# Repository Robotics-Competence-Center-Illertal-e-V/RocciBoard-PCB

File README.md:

# Rocci Board

# Features

* 4x DC Motor outputs a 3 A (motor driver with current limitation)
* 8 separate i2c channels
* low voltage shutdown for battery protection
* i2c fully protected against 12V and reverse polarity
* 3 A switching regulator for 5 V
* 3,3 V with 1 A LDO
* 8 V for Arduino VIN pin
* reverse polarity protection on battery connector
* short circuit protection on all supply pins

# Schematic

[Schematic as pdf](documentation/RocciBoard.pdf)

[Layout as pdf](documentation/RocciBoard__Assembly.pdf)

# Pinout Diagram

## Top

## Bottom

## Hand Assembled Components

male pinheader with femal back:
1* 4
1* 7
2* 8
1* 18x2

male pinheader:
1* 8
1* 10
1* 4
1* 1
9* 4
4* 2

1* XT60 Male

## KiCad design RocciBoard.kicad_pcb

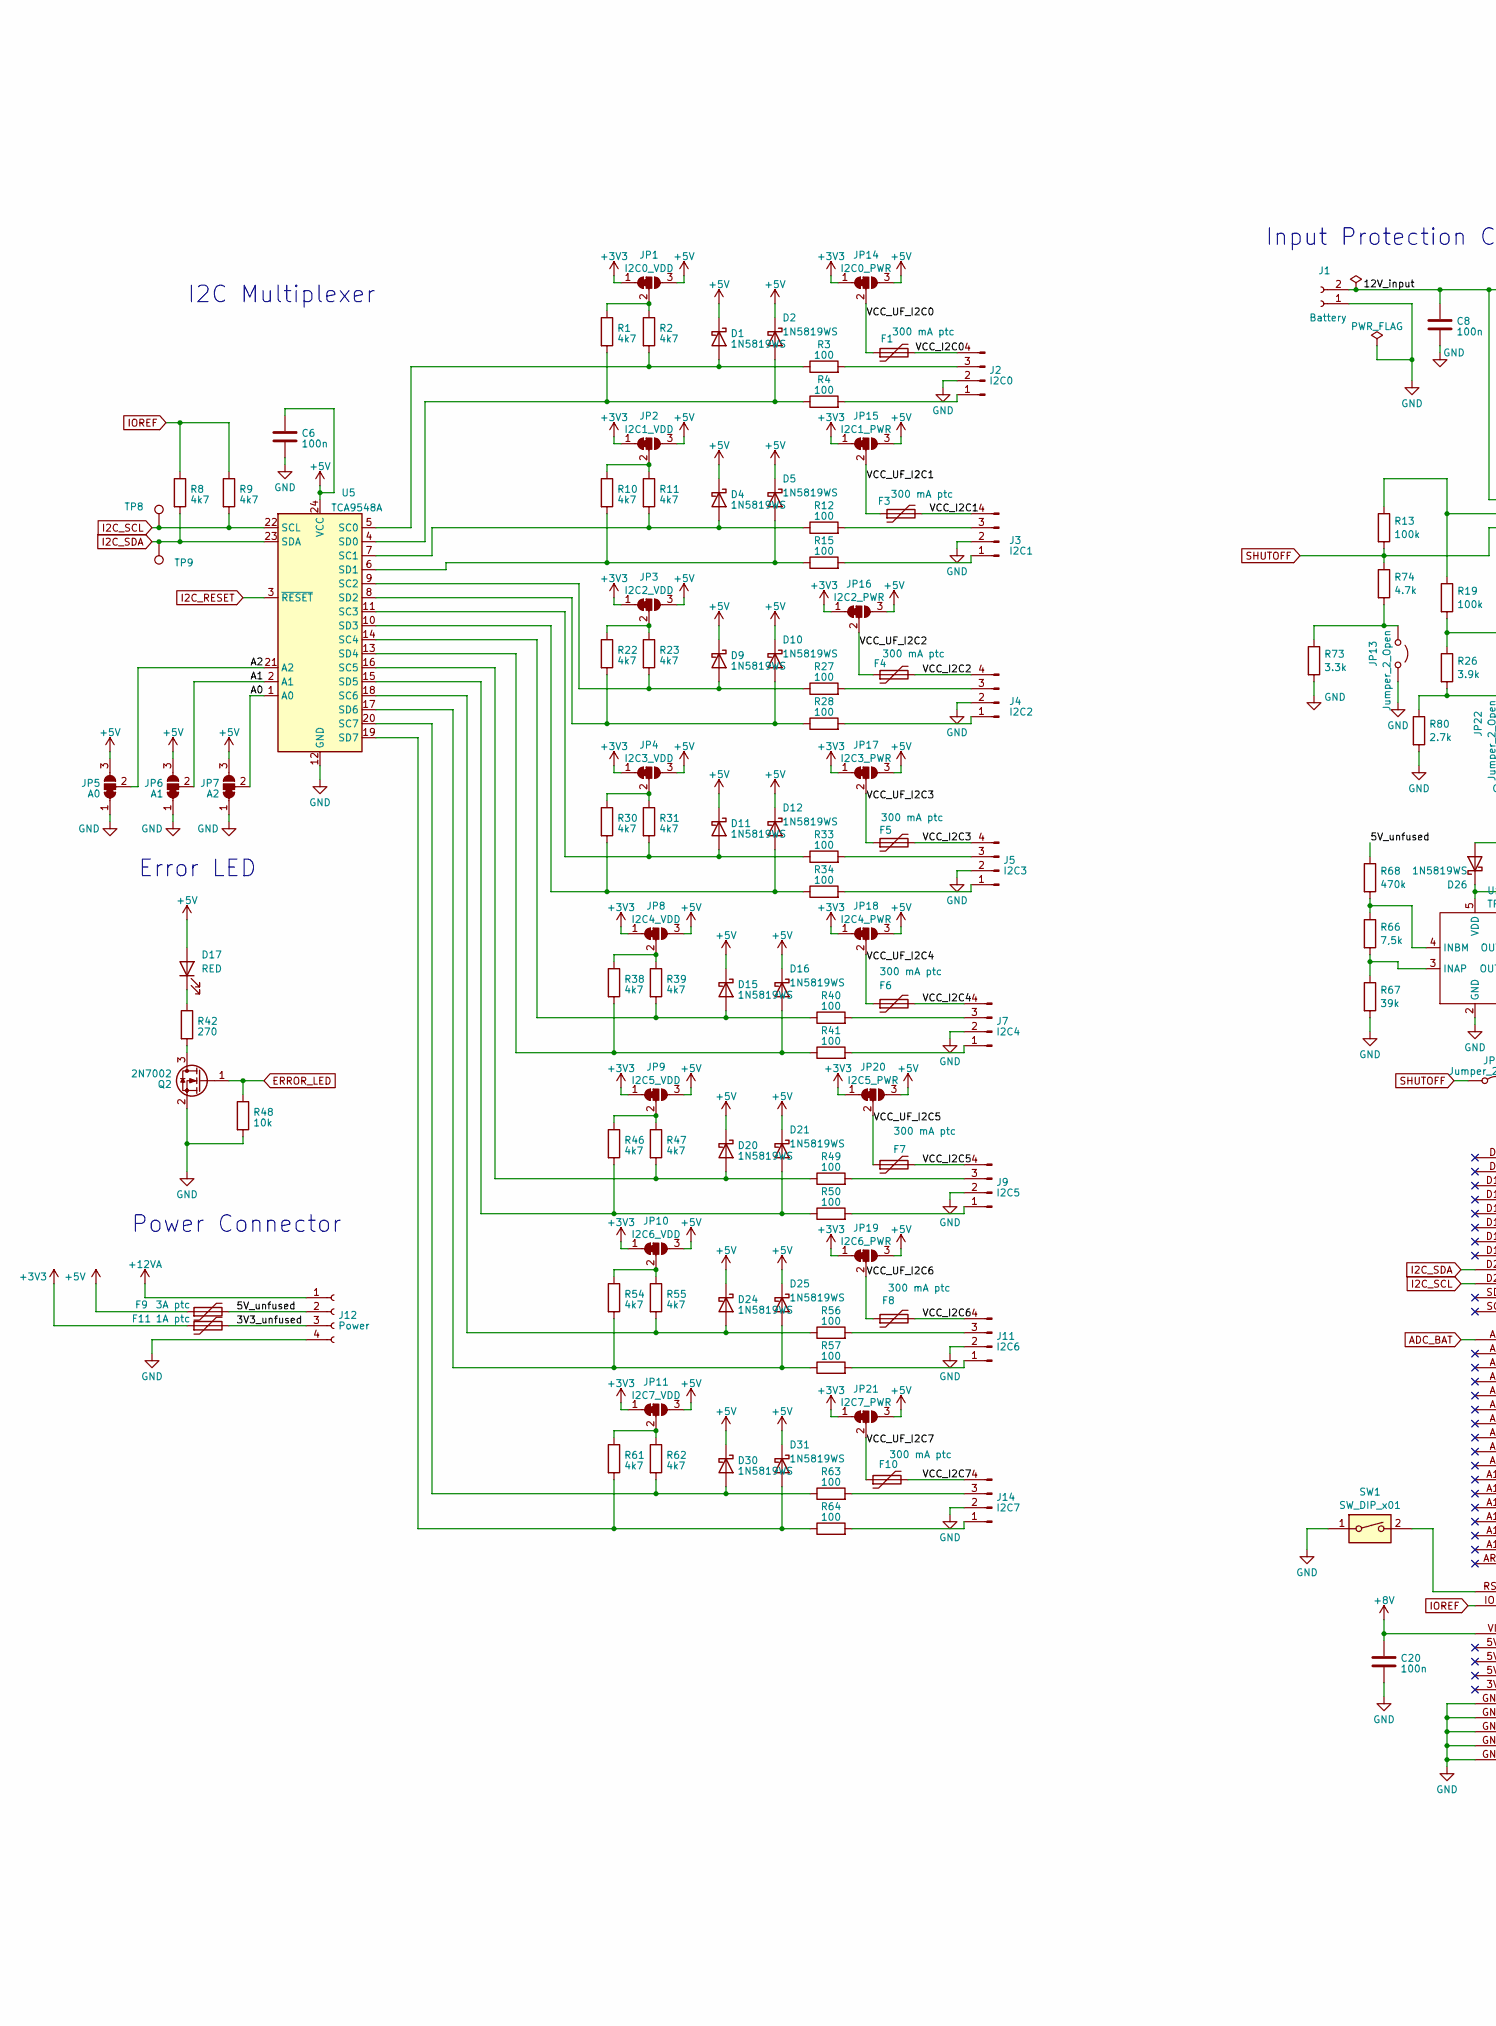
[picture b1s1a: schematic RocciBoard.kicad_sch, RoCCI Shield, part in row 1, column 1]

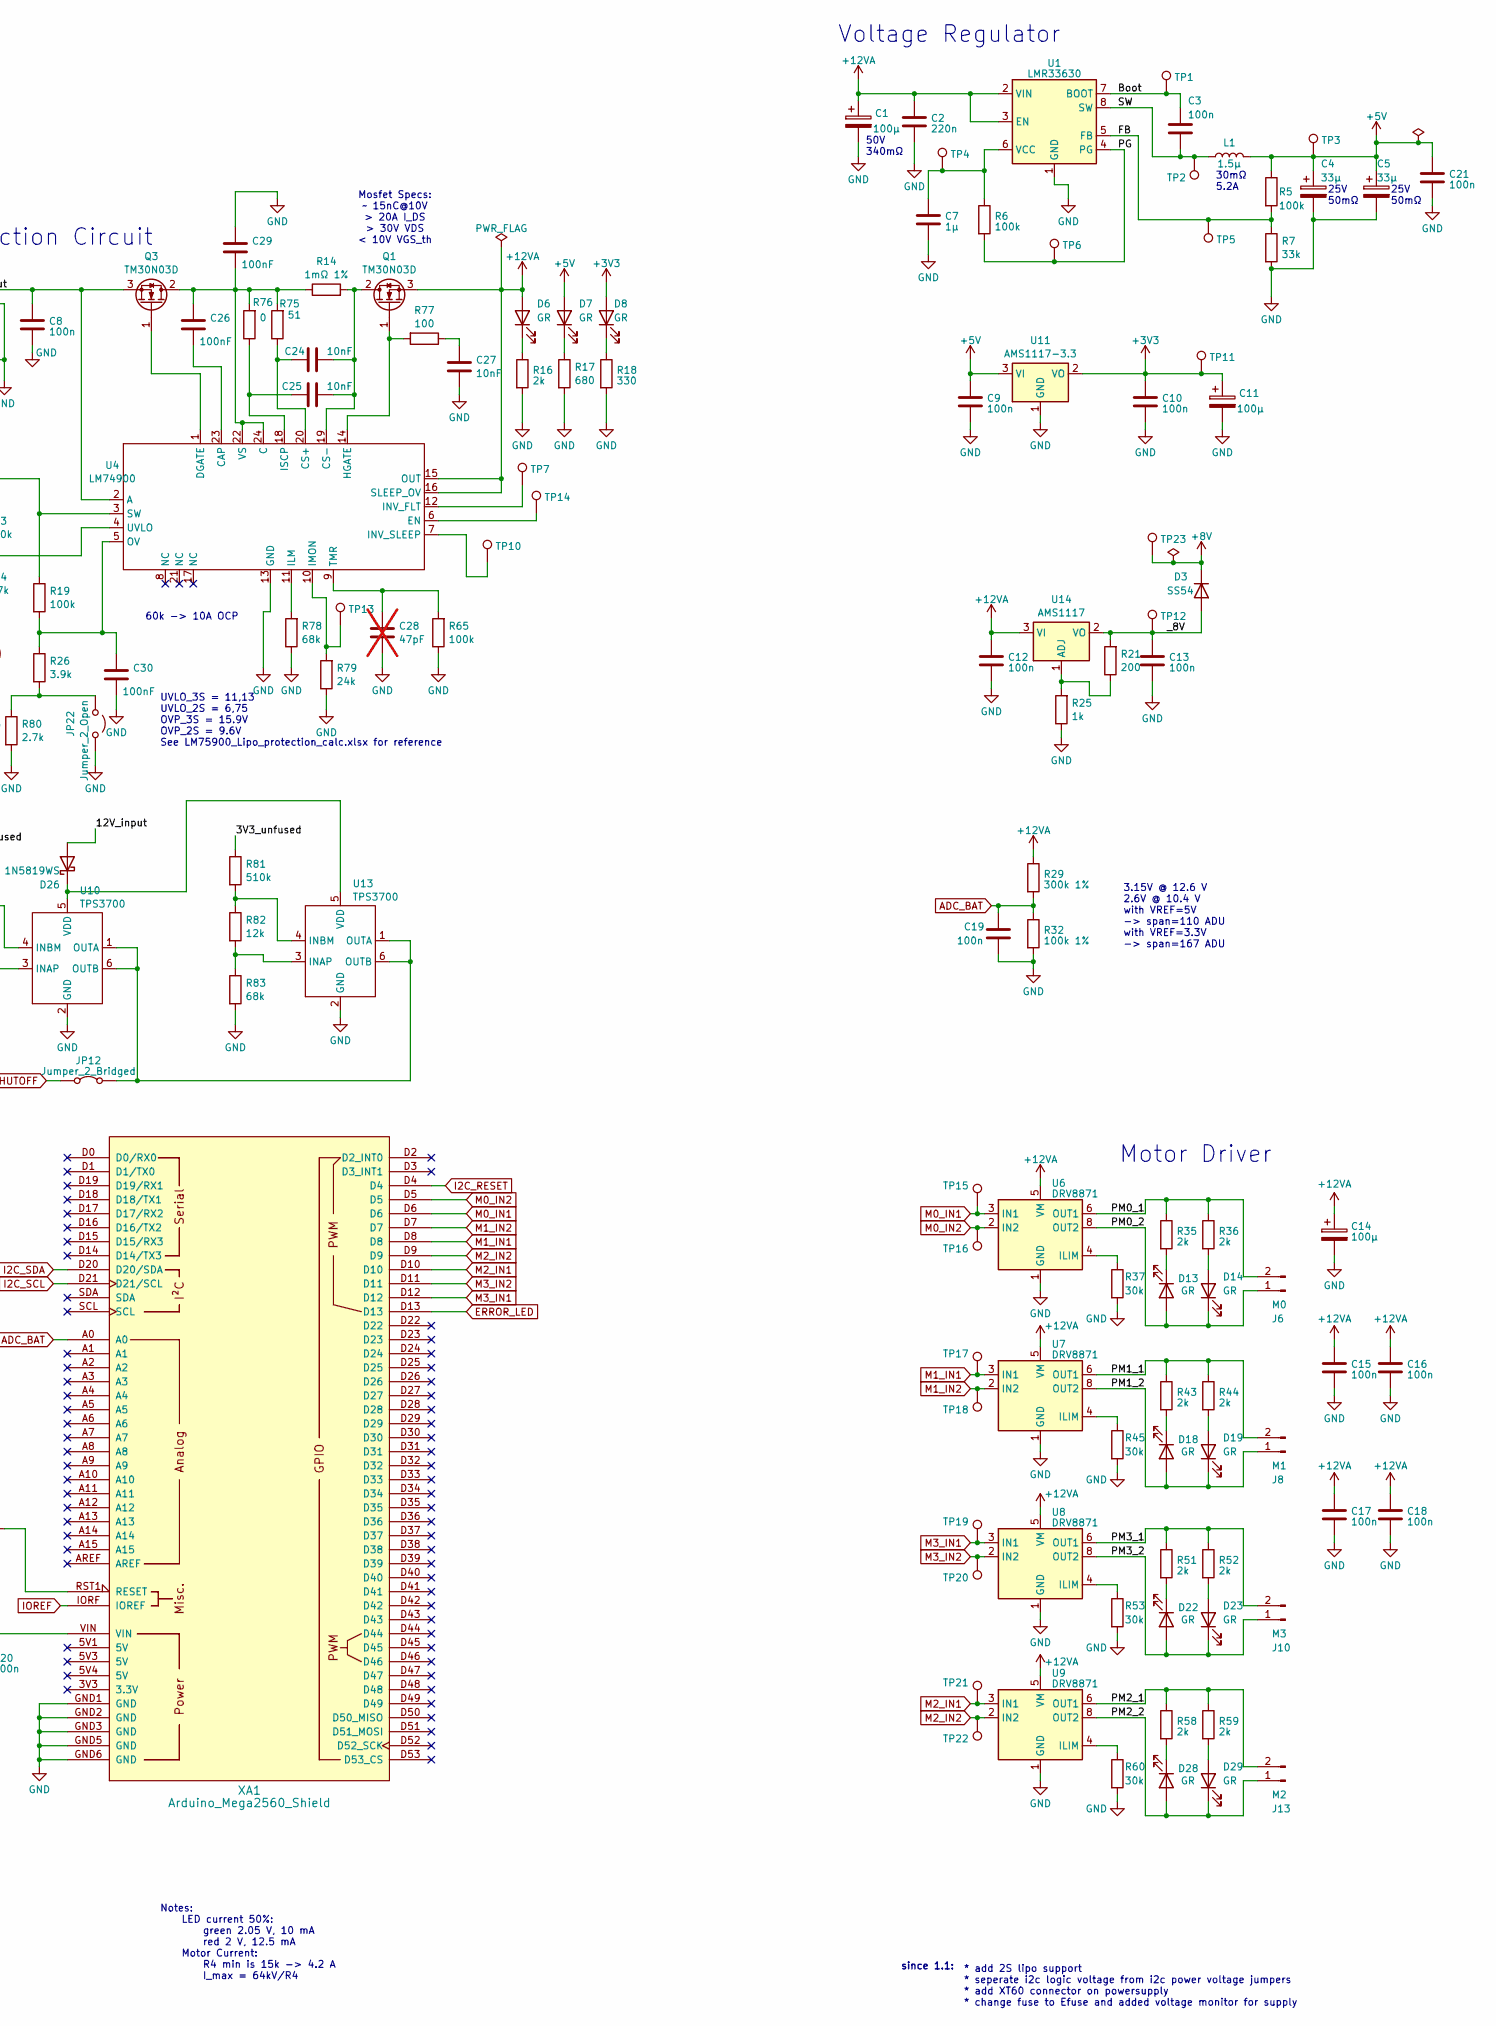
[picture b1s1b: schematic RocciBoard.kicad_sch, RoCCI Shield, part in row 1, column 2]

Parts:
C1, C11, C14: 100µ; CP_Elec_6.3x7.7; LCSC C962164
C2: 220n; C_0603_1608Metric; LCSC C21120
C3, C6, C8, C9, C10, C12, C13, C15, C16, C17, C18, C19, C20, C21: 100n; C_0603_1608Metric; LCSC C14663
C4, C5: 33µ; CP_EIA-7343-43_Kemet-X; LCSC C212716
C7: 1µ; C_0603_1608Metric; LCSC C15849
C24, C25, C27: 10nF; C_0603_1608Metric; LCSC C57112
C26, C29, C30: 100nF; C_0603_1608Metric; LCSC C14663
C28: 47pF; C_0603_1608Metric; LCSC C1671; not fitted
D1, D2, D4, D5, D9, D10, D11, D12, D15, D16, D20, D21, D24, D25, D26, D30, D31: 1N5819WS; D_SOD-323; LCSC C191023
D3: SS54; D_SMA; LCSC C22452
D6, D7, D8, D13, D14, D18, D19, D22, D23, D28, D29: GR; LED_0603_1608Metric; LCSC C965805
D17: RED; LED_0603_1608Metric; LCSC C2286
F1, F3, F4, F5, F6, F7, F8, F10: 300 mA ptc; Fuse_0805_2012Metric; LCSC C261938
F9: 3A ptc; Fuse_2920_7451Metric; LCSC C2977527
F11: 1A ptc; Fuse_1206_3216Metric; LCSC C910830
J1: Battery; AMASS_XT60-M_1x02_P7.20mm_Vertical
J2: I2C0; PinHeader_1x04_P2.54mm_Vertical
J3: I2C1; PinHeader_1x04_P2.54mm_Vertical
J4: I2C2; PinHeader_1x04_P2.54mm_Vertical
J5: I2C3; PinHeader_1x04_P2.54mm_Vertical
J6: M0; PinHeader_1x02_P2.54mm_Vertical
J7: I2C4; PinHeader_1x04_P2.54mm_Vertical
J8: M1; PinHeader_1x02_P2.54mm_Vertical
J9: I2C5; PinHeader_1x04_P2.54mm_Vertical
J10: M3; PinHeader_1x02_P2.54mm_Vertical
J11: I2C6; PinHeader_1x04_P2.54mm_Vertical
J12: Power; PinHeader_1x04_P2.54mm_Vertical
J13: M2; PinHeader_1x02_P2.54mm_Vertical
J14: I2C7; PinHeader_1x04_P2.54mm_Vertical
JP1: I2C0_VDD; SolderJumper-3_P1.3mm_Open_Pad1.0x1.5mm
JP2: I2C1_VDD; SolderJumper-3_P1.3mm_Open_Pad1.0x1.5mm
JP3: I2C2_VDD; SolderJumper-3_P1.3mm_Open_Pad1.0x1.5mm
JP4: I2C3_VDD; SolderJumper-3_P1.3mm_Open_Pad1.0x1.5mm
JP5: A0; SolderJumper-3_P1.3mm_Open_Pad1.0x1.5mm
JP6: A1; SolderJumper-3_P1.3mm_Open_Pad1.0x1.5mm
JP7: A2; SolderJumper-3_P1.3mm_Open_Pad1.0x1.5mm
JP8: I2C4_VDD; SolderJumper-3_P1.3mm_Open_Pad1.0x1.5mm
JP9: I2C5_VDD; SolderJumper-3_P1.3mm_Open_Pad1.0x1.5mm
JP10: I2C6_VDD; SolderJumper-3_P1.3mm_Open_Pad1.0x1.5mm
JP11: I2C7_VDD; SolderJumper-3_P1.3mm_Open_Pad1.0x1.5mm
JP12: Jumper_2_Bridged; SolderJumper-2_P1.3mm_Open_Pad1.0x1.5mm
JP13, JP22: Jumper_2_Open; SolderJumper-2_P1.3mm_Open_Pad1.0x1.5mm
JP14: I2C0_PWR; SolderJumper-3_P1.3mm_Open_Pad1.0x1.5mm
JP15: I2C1_PWR; SolderJumper-3_P1.3mm_Open_Pad1.0x1.5mm
JP16: I2C2_PWR; SolderJumper-3_P1.3mm_Open_Pad1.0x1.5mm
JP17: I2C3_PWR; SolderJumper-3_P1.3mm_Open_Pad1.0x1.5mm
JP18: I2C4_PWR; SolderJumper-3_P1.3mm_Open_Pad1.0x1.5mm
JP19: I2C6_PWR; SolderJumper-3_P1.3mm_Open_Pad1.0x1.5mm
JP20: I2C5_PWR; SolderJumper-3_P1.3mm_Open_Pad1.0x1.5mm
JP21: I2C7_PWR; SolderJumper-3_P1.3mm_Open_Pad1.0x1.5mm
L1: 1.5µ; L_Sunlord_SWPA4020S; LCSC C98360
Q1, Q3: TM30N03D; TO-252-2; LCSC C18186756
Q2: 2N7002; SOT-23; LCSC C8545
R1, R2, R8, R9, R10, R11, R22, R23, R30, R31, R38, R39, R46, R47, R54, R55, R61, R62: 4k7; R_0603_1608Metric; LCSC C23162
R3, R4, R12, R15, R27, R28, R33, R34, R40, R41, R49, R50, R56, R57, R63, R64, R77: 100; R_0603_1608Metric; LCSC C22775
R5, R6, R13, R19, R65: 100k; R_0603_1608Metric; LCSC C25803
R7: 33k; R_0603_1608Metric; LCSC C4216
R14: 1mΩ 1%; R_1206_3216Metric; LCSC C7467246
R16, R35, R36, R43, R44, R51, R52, R58, R59: 2k; R_0603_1608Metric; LCSC C22975
R17: 680; R_0603_1608Metric; LCSC C23228
R18: 330; R_0603_1608Metric; LCSC C23138
R21: 200; R_0603_1608Metric; LCSC C8218
R25: 1k; R_0603_1608Metric; LCSC C21190
R26: 3.9k; R_0603_1608Metric; LCSC C23018
R29: 300k 1%; R_0603_1608Metric; LCSC C23024
R32: 100k 1%; R_0603_1608Metric; LCSC C25803
R37, R45, R53, R60: 30k; R_0805_2012Metric; LCSC C22984
R42: 270; R_0603_1608Metric; LCSC C22966
R48: 10k; R_0603_1608Metric; LCSC C25804
R66: 7,5k; R_0603_1608Metric; LCSC C23234
R67: 39k; R_0603_1608Metric; LCSC C23153
R68: 470k; R_0603_1608Metric; LCSC C23178
R73: 3.3k; R_0603_1608Metric; LCSC C22978
R74: 4.7k; R_0603_1608Metric; LCSC C23162
R75: 51; R_0603_1608Metric; LCSC C23197
R76: 0; R_0603_1608Metric; LCSC C21189
R78, R83: 68k; R_0603_1608Metric; LCSC C23231
R79: 24k; R_0603_1608Metric; LCSC C23352
R80: 2.7k; R_0603_1608Metric; LCSC C13167
R81: 510k; R_0603_1608Metric; LCSC C23192
R82: 12k; R_0603_1608Metric; LCSC C22790
SW1: SW_DIP_x01; SW_Push_1P1T_XKB_TS-1187A; LCSC C318884
TP1, TP2, TP3, TP4, TP5, TP6, TP7, TP8, TP9, TP10, TP11, TP12, TP13, TP14, TP15, TP16, TP17, TP18, TP19, TP20, TP21, TP22, TP23: TestPoint_Pad_D1.0mm
U1: LMR33630; Texas_HSOP-8-1EP_3.9x4.9mm_P1.27mm_ThermalVias; LCSC C841384
U4: LM74900; VQFN-24-1EP_4x4mm_P0.5mm_EP2.5x2.5mm_ThermalVias; LCSC C20345498
U5: TCA9548A; TSSOP-24_4.4x7.8mm_P0.65mm; LCSC C130026
U6, U7, U8, U9: DRV8871; Texas_HTSOP-8-1EP_3.9x4.9mm_P1.27mm_EP2.95x4.9mm_Mask2.4x3.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; LCSC C75864
U10, U13: TPS3700; SOT-23-6; LCSC C33002
U11: AMS1117-3.3; SOT-223-3_TabPin2; LCSC C6186
U14: AMS1117; SOT-223-3_TabPin2; LCSC C347224
XA1: Arduino_Mega2560_Shield; Arduino_Mega2560_custom_Shield

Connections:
+3V3: C10.1, C11.1, D8.2 (A), F11.1, JP1.1 (A), JP2.1 (A), JP3.1 (A), JP4.1 (A), JP8.1 (A), JP9.1 (A), JP10.1 (A), JP11.1 (A), JP14.1 (A), JP15.1 (A), JP16.1 (A), JP17.1 (A), JP18.1 (A), JP19.1 (A), JP20.1 (A), JP21.1 (A), TP11.1, U11.2 (VO)
+5V: C4.1, C5.1, C6.1, C9.1, C21.1, D1.1 (K), D2.1 (K), D4.1 (K), D5.1 (K), D7.2 (A), D9.1 (K), D10.1 (K), D11.1 (K), D12.1 (K), D15.1 (K), D16.1 (K), D17.2 (A), D20.1 (K), D21.1 (K), D24.1 (K), D25.1 (K), D30.1 (K), D31.1 (K), F9.1, JP1.3 (B), JP2.3 (B), JP3.3 (B), JP4.3 (B), JP5.3 (B), JP6.3 (B), JP7.3 (B), JP8.3 (B), JP9.3 (B), JP10.3 (B), JP11.3 (B), JP14.3 (B), JP15.3 (B), JP16.3 (B), JP17.3 (B), JP18.3 (B), JP19.3 (B), JP20.3 (B), JP21.3 (B), L1.2, R5.1, TP3.1, U5.24 (VCC), U11.3 (VI)
+8V: C20.1, D3.1 (K), TP23.1, XA1.VIN
+12VA: C1.1, C2.1, C12.1, C14.1, C15.1, C16.1, C17.1, C18.1, D6.2 (A), J12.1, Q1.3 (S), R29.1, U1.2 (VIN), U1.3 (EN), U4.15 (OUT), U4.16 (SLEEP_OV), U6.5 (VM), U7.5 (VM), U8.5 (VM), U9.5 (VM), U14.3 (VI)
/3V3_unfused: F11.2, J12.3, R81.1
/5V_unfused: F9.2, J12.2, R68.1
/12V_input: C8.1, D26.2 (A), J1.2, Q3.3 (S), U4.2 (A)
/A0: JP7.2 (C), U5.1 (A0)
/A1: JP6.2 (C), U5.2 (A1)
/A2: JP5.2 (C), U5.21 (A2)
/Boot: C3.1, TP1.1, U1.7 (BOOT)
/FB: R5.2, R7.1, TP5.1, U1.5 (FB)
/PG: R6.2, TP6.1, U1.4 (PG)
/PM0_1: J6.2, R35.1, R36.1, U6.6 (OUT1)
/PM0_2: D13.2 (A), D14.1 (K), J6.1, U6.8 (OUT2)
/PM1_1: J8.2, R43.1, R44.1, U7.6 (OUT1)
/PM1_2: D18.2 (A), D19.1 (K), J8.1, U7.8 (OUT2)
/PM2_1: J13.2, R58.1, R59.1, U9.6 (OUT1)
/PM2_2: D28.2 (A), D29.1 (K), J13.1, U9.8 (OUT2)
/PM3_1: J10.2, R51.1, R52.1, U8.6 (OUT1)
/PM3_2: D22.2 (A), D23.1 (K), J10.1, U8.8 (OUT2)
/SW: C3.2, L1.1, TP2.1, U1.8 (SW)
/VCC_I2C0: F1.2, J2.4
/VCC_I2C1: F3.2, J3.4
/VCC_I2C2: F4.2, J4.4
/VCC_I2C3: F5.2, J5.4
/VCC_I2C4: F6.2, J7.4
/VCC_I2C5: F7.2, J9.4
/VCC_I2C6: F8.2, J11.4
/VCC_I2C7: F10.2, J14.4
/VCC_UF_I2C0: F1.1, JP14.2 (C)
/VCC_UF_I2C1: F3.1, JP15.2 (C)
/VCC_UF_I2C2: F4.1, JP16.2 (C)
/VCC_UF_I2C3: F5.1, JP17.2 (C)
/VCC_UF_I2C4: F6.1, JP18.2 (C)
/VCC_UF_I2C5: F7.1, JP20.2 (C)
/VCC_UF_I2C6: F8.1, JP19.2 (C)
/VCC_UF_I2C7: F10.1, JP21.2 (C)
/_8V: C13.1, D3.2 (A), R21.2, TP12.1, U14.2 (VO)
ADC_BAT: C19.2, R29.2, R32.1, XA1.A0
ERROR_LED: Q2.1 (G), R48.1, XA1.D13
GND: C1.2, C2.2, C4.2, C5.2, C6.2, C7.2, C8.2, C9.2, C10.2, C11.2, C12.2, C13.2, C14.2, C15.2, C16.2, C17.2, C18.2, C19.1, C20.2, C21.2, C27.2, C28.2, C29.1, C30.2, J1.1, J2.2, J3.2, J4.2, J5.2, J7.2, J9.2, J11.2, J12.4, J14.2, JP5.1 (A), JP6.1 (A), JP7.1 (A), JP13.2 (B), JP22.2 (B), Q2.2 (S), R7.2, R16.2, R17.2, R18.2, R25.1, R32.2, R37.2, R45.2, R48.2, R53.2, R60.2, R65.1, R67.2, R73.2, R78.1, R79.1, R80.2, R83.2, SW1.1, U1.1 (GND), U1.9 (GND), U4.13 (GND), U5.12 (GND), U6.1 (GND), U6.7 (GND), U6.9 (GND), U7.1 (GND), U7.7 (GND), U7.9 (GND), U8.1 (GND), U8.7 (GND), U8.9 (GND), U9.1 (GND), U9.7 (GND), U9.9 (GND), U10.2 (GND), U11.1 (GND), U13.2 (GND), XA1.GND1 (GND), XA1.GND2 (GND), XA1.GND3 (GND), XA1.GND5 (GND), XA1.GND6 (GND)
I2C_RESET: U5.3 (~RESET), XA1.D4
I2C_SCL: R9.2, TP8.1, U5.22 (SCL), XA1.D21 (D21/SCL)
I2C_SDA: R8.2, TP9.1, U5.23 (SDA), XA1.D20 (D20/SDA)
IOREF: R8.1, R9.1, XA1.IORF (IOREF)
M0_IN1: TP15.1, U6.3 (IN1), XA1.D6
M0_IN2: TP16.1, U6.2 (IN2), XA1.D5
M1_IN1: TP17.1, U7.3 (IN1), XA1.D8
M1_IN2: TP18.1, U7.2 (IN2), XA1.D7
M2_IN1: TP21.1, U9.3 (IN1), XA1.D10
M2_IN2: TP22.1, U9.2 (IN2), XA1.D9
M3_IN1: TP19.1, U8.3 (IN1), XA1.D12
M3_IN2: TP20.1, U8.2 (IN2), XA1.D11
unnamed: C27.1, R77.1
unnamed: D1.2 (A), R2.2, R3.1, U5.5 (SC0)
unnamed: D2.2 (A), R1.2, R4.1, U5.4 (SD0)
unnamed: D4.2 (A), R11.2, R12.1, U5.7 (SC1)
unnamed: D5.2 (A), R10.2, R15.1, U5.6 (SD1)
unnamed: D6.1 (K), R16.1
unnamed: D7.1 (K), R17.1
unnamed: D8.1 (K), R18.1
unnamed: D9.2 (A), R23.2, R27.1, U5.9 (SC2)
unnamed: D10.2 (A), R22.2, R28.1, U5.8 (SD2)
unnamed: D11.2 (A), R31.2, R33.1, U5.11 (SC3)
unnamed: D12.2 (A), R30.2, R34.1, U5.10 (SD3)
unnamed: D13.1 (K), R35.2
unnamed: D14.2 (A), R36.2
unnamed: D15.2 (A), R39.2, R40.1, U5.14 (SC4)
unnamed: D16.2 (A), R38.2, R41.1, U5.13 (SD4)
unnamed: D17.1 (K), R42.1
unnamed: D18.1 (K), R43.2
unnamed: D19.2 (A), R44.2
unnamed: D20.2 (A), R47.2, R49.1, U5.16 (SC5)
unnamed: D21.2 (A), R46.2, R50.1, U5.15 (SD5)
unnamed: D22.1 (K), R51.2
unnamed: D23.2 (A), R52.2
unnamed: D24.2 (A), R55.2, R56.1, U5.18 (SC6)
unnamed: D25.2 (A), R54.2, R57.1, U5.17 (SD6)
unnamed: D26.1 (K), U10.5 (VDD), U13.5 (VDD)
unnamed: D28.1 (K), R58.2
unnamed: D29.2 (A), R59.2
unnamed: D30.2 (A), R62.2, R63.1, U5.20 (SC7)
unnamed: D31.2 (A), R61.2, R64.1, U5.19 (SD7)
unnamed: J2.1, R4.2
unnamed: J2.3, R3.2
unnamed: J3.1, R15.2
unnamed: J3.3, R12.2
unnamed: J4.1, R28.2
unnamed: J4.3, R27.2
unnamed: J5.1, R34.2
unnamed: J5.3, R33.2
unnamed: J7.1, R41.2
unnamed: J7.3, R40.2
unnamed: J9.1, R50.2
unnamed: J9.3, R49.2
unnamed: J11.1, R57.2
unnamed: J11.3, R56.2
unnamed: J14.1, R64.2
unnamed: J14.3, R63.2
unnamed: JP1.2 (C), R1.1, R2.1
unnamed: JP2.2 (C), R10.1, R11.1
unnamed: JP3.2 (C), R22.1, R23.1
unnamed: JP4.2 (C), R30.1, R31.1
unnamed: JP8.2 (C), R38.1, R39.1
unnamed: JP9.2 (C), R46.1, R47.1
unnamed: JP10.2 (C), R54.1, R55.1
unnamed: JP11.2 (C), R61.1, R62.1
unnamed: JP12.2 (B), U10.1 (OUTA), U10.6 (OUTB), U13.1 (OUTA), U13.6 (OUTB)
unnamed: JP13.1 (A), R73.1, R74.2
unnamed: JP22.1 (A), R26.2, R80.1
unnamed: C24.2, C25.2, Q1.2 (D), R14.2, U4.19 (CS-)
unnamed: Q1.1 (G), R77.2, U4.14 (HGATE)
unnamed: Q2.3 (D), R42.2
unnamed: C26.1, C29.2, Q3.2 (D), R14.1, R75.2, R76.2, U4.22 (VS), U4.24 (C)
unnamed: Q3.1 (G), U4.1 (DGATE)
unnamed: C7.1, R6.1, TP4.1, U1.6 (VCC)
unnamed: C26.2, U4.23 (CAP)
unnamed: C24.1, R75.1, U4.20 (CS+)
unnamed: TP14.1, U4.6 (EN)
unnamed: R78.2, U4.11 (ILM)
unnamed: R79.2, TP13.1, U4.10 (IMON)
unnamed: TP7.1, U4.12 (INV_FLT)
unnamed: TP10.1, U4.7 (INV_SLEEP)
unnamed: C25.1, R76.1, U4.18 (ISCP)
unnamed: C30.1, R19.2, R26.1, U4.5 (OV)
unnamed: R13.1, R19.1, U4.3 (SW)
unnamed: C28.1, R65.2, U4.9 (TMR)
unnamed: R37.1, U6.4 (ILIM)
unnamed: R45.1, U7.4 (ILIM)
unnamed: R53.1, U8.4 (ILIM)
unnamed: R60.1, U9.4 (ILIM)
unnamed: R66.2, R67.1, U10.3 (INAP)
unnamed: R66.1, R68.2, U10.4 (INBM)
unnamed: R82.2, R83.1, U13.3 (INAP)
unnamed: R81.2, R82.1, U13.4 (INBM)
unnamed: R21.1, R25.2, U14.1 (ADJ)
unnamed: SW1.2, XA1.RST1 (RESET)
SHUTOFF: JP12.1 (A), R13.2, R74.1, U4.4 (UVLO)

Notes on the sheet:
Notes: LED current 50%: green 2.05 V, 10 mA red 2 V, 12.5 mA Motor Current: R4 min is 15k -> 4.2 A I_max = 64kV/R4
Error LED
30mΩ 5.2A
Mosfet Specs: ~ 15nC@10V > 20A I_DS > 30V VDS < 10V VGS_th
3.15V @ 12.6 V 2.6V @ 10.4 V with VREF=5V -> span=110 ADU with VREF=3.3V -> span=167 ADU
Motor Driver
since 1.1:
50V 340mΩ
60k -> 10A OCP
UVLO_3S = 11,13 UVLO_2S = 6,75 OVP_3S = 15.9V OVP_2S = 9.6V See LM75900_Lipo_protection_calc.xlsx for reference
Input Protection Circuit
25V 50mΩ
I2C Multiplexer
Power Connector
* add 2S lipo support * seperate i2c logic voltage from i2c power voltage jumpers * add XT60 connector on powersupply * change fuse to Efuse and added voltage monitor for supply
Voltage Regulator

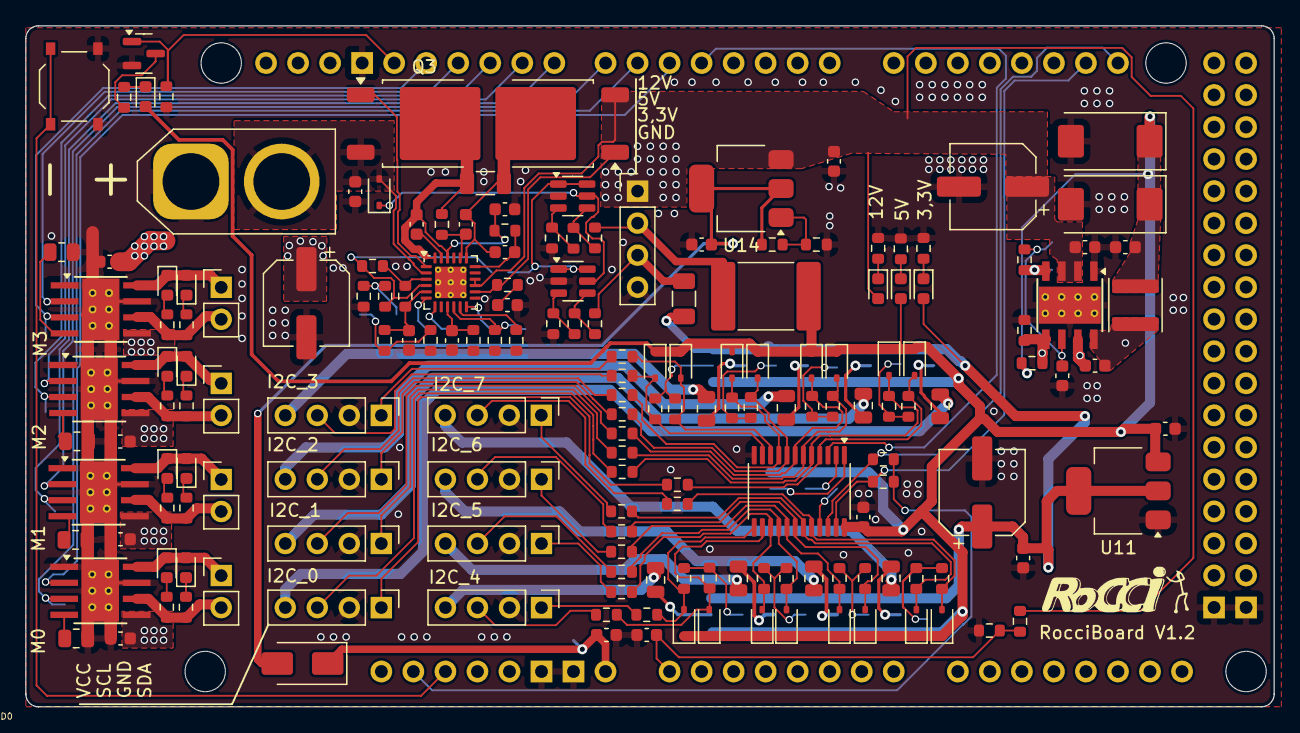
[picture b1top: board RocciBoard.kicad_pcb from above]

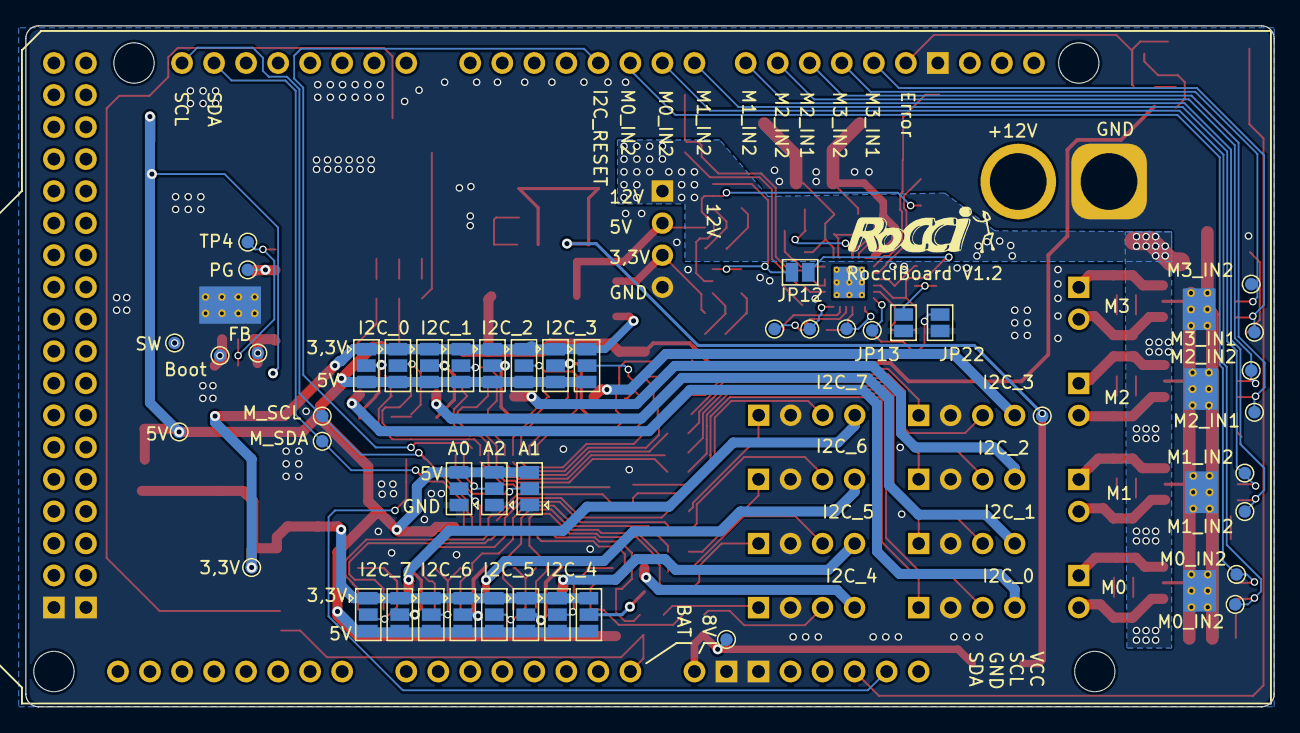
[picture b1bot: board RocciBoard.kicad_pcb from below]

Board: 2 copper layers, 99.0 x 54.0 mm, 221 parts (45 on the bottom side), 139 nets.

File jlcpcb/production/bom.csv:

Designator,Footprint,Quantity,Value,LCSC Part #
"C1, C11, C14",CP_Elec_6.3x7.7,3,100µ,C962164
"C10, C12, C13, C15, C16, C17, C18, C19, C20, C21, C3, C6, C8, C9",0603,14,100n,C14663
C2,0603,1,220n,C21120
"C4, C5",CP_EIA-7343-43_Kemet-X,2,33µ,C212716
C7,0603,1,1µ,C15849
"D1, D10, D11, D12, D15, D16, D2, D20, D21, D24, D25, D30, D31, D4, D5, D9",D_SOD-323,16,1N5819WS,C191023
"D13, D14, D18, D19, D22, D23, D28, D29, D6, D7, D8",0603,11,GR,C72043
D17,0603,1,RED,C2286
D3,D_SMA,1,SS54,C22452
D32,TO-277A,1,SB10100L,C113946
"F1, F10, F3, F4, F5, F6, F7, F8",0805,8,300 mA ptc,C261938
F11,1206,1,1A ptc,C910830
F2,Fuseholder_Cylinder-5x20mm_Wuerth_696103101002-SMD_Horizontal_Open,1,10A,C122783
F9,2920,1,3A ptc,C2977527
J1,"PhoenixContact_MSTBVA_2,5_2-G_1x02_P5.00mm_Vertical",1,Battery,
J10,PinHeader_1x02_P2.54mm_Vertical,1,M3,
J11,PinHeader_1x04_P2.54mm_Vertical,1,I2C6,
J12,PinHeader_1x04_P2.54mm_Vertical,1,Power,
J13,PinHeader_1x02_P2.54mm_Vertical,1,M2,
J14,PinHeader_1x04_P2.54mm_Vertical,1,I2C7,
J2,PinHeader_1x04_P2.54mm_Vertical,1,I2C0,
J3,PinHeader_1x04_P2.54mm_Vertical,1,I2C1,
J4,PinHeader_1x04_P2.54mm_Vertical,1,I2C2,
J5,PinHeader_1x04_P2.54mm_Vertical,1,I2C3,
J6,PinHeader_1x02_P2.54mm_Vertical,1,M0,
J7,PinHeader_1x04_P2.54mm_Vertical,1,I2C4,
J8,PinHeader_1x02_P2.54mm_Vertical,1,M1,
J9,PinHeader_1x04_P2.54mm_Vertical,1,I2C5,
JP1,SolderJumper-3_P1.3mm_Open_Pad1.0x1.5mm,1,I2C0_VCC,
JP10,SolderJumper-3_P1.3mm_Open_Pad1.0x1.5mm,1,I2C6_VCC,
JP11,SolderJumper-3_P1.3mm_Open_Pad1.0x1.5mm,1,I2C7_VCC,
JP12,SolderJumper-2_P1.3mm_Open_Pad1.0x1.5mm,1,Jumper_2_Bridged,
JP2,SolderJumper-3_P1.3mm_Open_Pad1.0x1.5mm,1,I2C1_VCC,
JP3,SolderJumper-3_P1.3mm_Open_Pad1.0x1.5mm,1,I2C2_VCC,
JP4,SolderJumper-3_P1.3mm_Open_Pad1.0x1.5mm,1,I2C3_VCC,
JP5,SolderJumper-3_P1.3mm_Open_Pad1.0x1.5mm,1,A0,
JP6,SolderJumper-3_P1.3mm_Open_Pad1.0x1.5mm,1,A1,
JP7,SolderJumper-3_P1.3mm_Open_Pad1.0x1.5mm,1,A2,
JP8,SolderJumper-3_P1.3mm_Open_Pad1.0x1.5mm,1,I2C4_VCC,
JP9,SolderJumper-3_P1.3mm_Open_Pad1.0x1.5mm,1,I2C5_VCC,
L1,L_Sunlord_SWPA4020S,1,1.5µ,C98360
Q1,SOIC-8_3.9x4.9mm_P1.27mm,1,IRF 7424,C148149
Q2,SOT-23,1,2N7002,C8545
"R1, R10, R11, R2, R22, R23, R30, R31, R38, R39, R46, R47, R54, R55, R61, R62, R8, R9",0603,18,4k7,C23162
"R12, R15, R27, R28, R3, R33, R34, R4, R40, R41, R49, R50, R56, R57, R63, R64",0603,16,100,C22775
R13,0603,1,4700k 1%,C23163
"R14, R48",0603,2,10k,C25804
"R16, R35, R36, R43, R44, R51, R52, R58, R59, R72",0603,10,2k,C22975
R17,0603,1,620,C23228
R18,0603,1,330,C23138
R19,0603,1,10k 1%,C25804
"R20, R21",0603,2,240,C23350
R24,0603,1,390,C23151
"R25, R70",0603,2,1k3,C22767
R26,0603,1,180k 1%,C22827
R29,0603,1,300k 1%,C23024
R32,0603,1,100k 1%,C25803
"R37, R45, R53, R60",0805,4,30k,C22984
R42,0603,1,270,C22966
"R5, R6",0603,2,100k,C25803
"R65, R71",0603,2,1k,C21190
R69,0603,1,1k5,C22843
R7,0603,1,24.9k,C25962
RESET,SW_Push_1P1T_XKB_TS-1187A,1,SW_DIP_x01,C318884
"TP1, TP10, TP11, TP12, TP13, TP14, TP15, TP16, TP17, TP18, TP19, TP2, TP20, TP21, TP22, TP23, TP3, TP4, TP5, TP6, TP7, TP8, TP9",TestPoint_Pad_D1.0mm,23,~,
U1,Texas_HSOP-8-1EP_3.9x4.9mm_P1.27mm_ThermalVias,1,LMR33630,C841384
"U11, U12",SOT-23,2,CJ431,C3113
"U2, U3",TO-252-2,2,LM317_TO-252,C75510
U4,SOT-23-6,1,TPS3700,C3658987
U5,TSSOP-24_4.4x7.8mm_P0.65mm,1,TCA9548A,C130026
"U6, U7, U8, U9",Texas_HTSOP-8-1EP_3.9x4.9mm_P1.27mm_EP2.95x4.9mm_Mask2.4x3.1mm_ThermalVias,4,DRV8871,C75864
XA1,Arduino_Mega2560_custom_Shield,1,Arduino_Mega2560_Shield,

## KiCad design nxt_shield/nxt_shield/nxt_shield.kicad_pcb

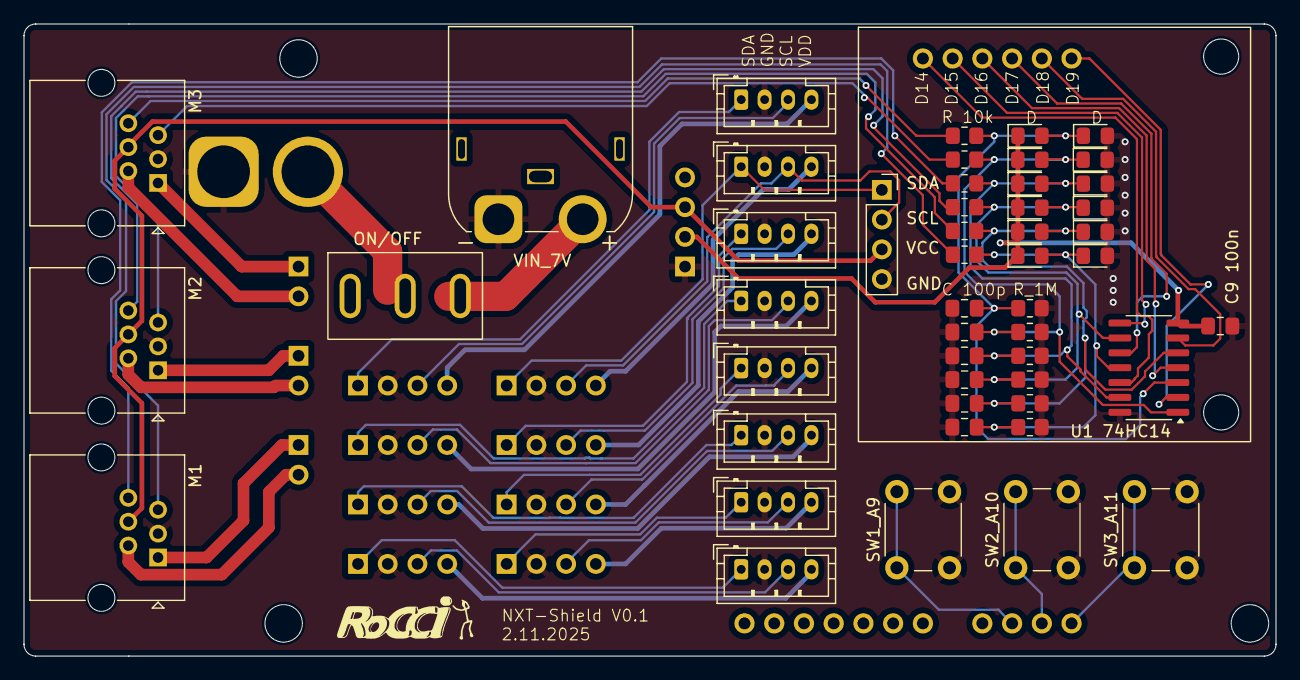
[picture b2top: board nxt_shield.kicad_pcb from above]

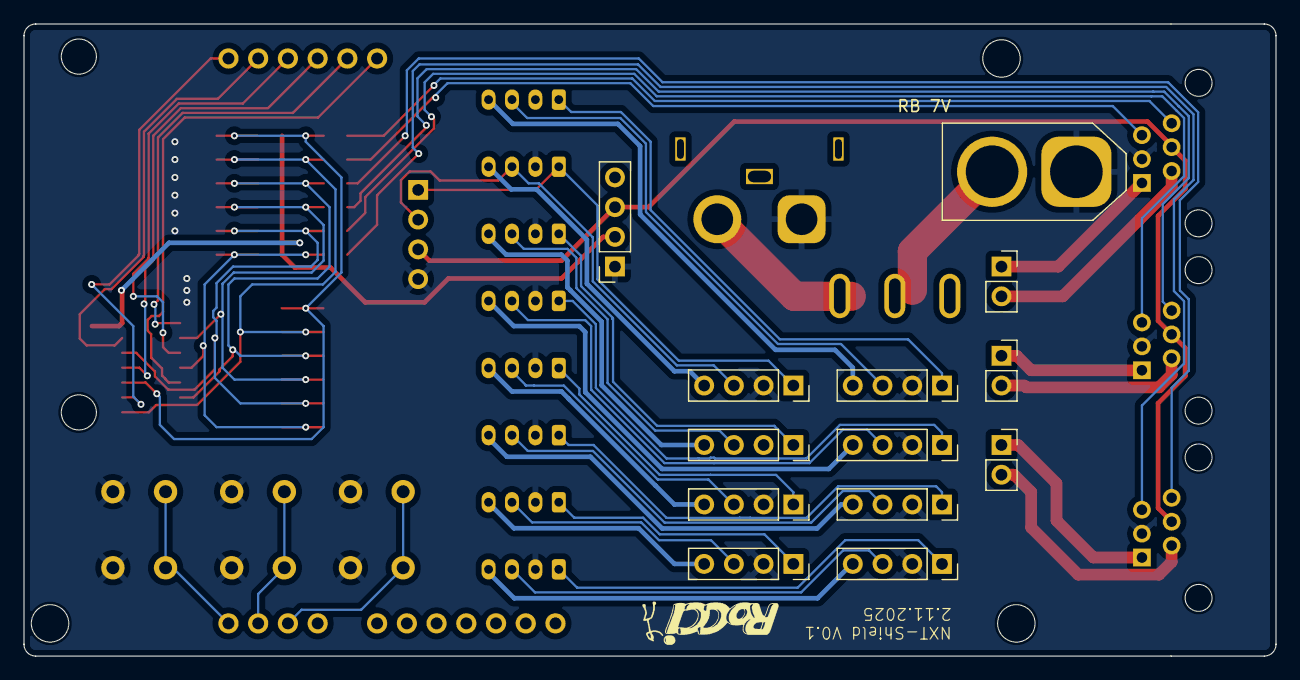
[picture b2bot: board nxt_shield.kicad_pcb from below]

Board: 2 copper layers, 107.0 x 54.0 mm, 63 parts (13 on the bottom side), 56 nets.

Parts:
A1: Arduino_Due_Shield
C1, C2, C3, C4, C5, C6: 100p; C_0805_2012Metric_Pad1.18x1.45mm_HandSolder
C9 100n: 100n; C_0805_2012Metric_Pad1.18x1.45mm_HandSolder
D1, D2, D3, D4, D6, D7, D8, D9, D10, D11, D12, D13: D; D_0805_2012Metric_Pad1.15x1.40mm_HandSolder
J3: XT60_PCB; AMASS_XT60-M_1x02_P7.20mm_Vertical
J4: RB_M2; PinSocket_1x02_P2.54mm_Vertical
J6: RB_M1; PinSocket_1x02_P2.54mm_Vertical
J8: LCD; OLE_LCD
J9: JST_RB_I2C0; JST_PH_B4B-PH-K_1x04_P2.00mm_Vertical
J13: JST_RB_I2C1; JST_PH_B4B-PH-K_1x04_P2.00mm_Vertical
J14: JST_RB_I2C2; JST_PH_B4B-PH-K_1x04_P2.00mm_Vertical
J15: JST_RB_I2C3; JST_PH_B4B-PH-K_1x04_P2.00mm_Vertical
J16: JST_RB_I2C4; JST_PH_B4B-PH-K_1x04_P2.00mm_Vertical
J17: RB_I2C1; PinSocket_1x04_P2.54mm_Vertical
J18: RB_I2C0; PinSocket_1x04_P2.54mm_Vertical
J19: RB_I2C2; PinSocket_1x04_P2.54mm_Vertical
J20: RB_I2C3; PinSocket_1x04_P2.54mm_Vertical
J21: RB_I2C4; PinSocket_1x04_P2.54mm_Vertical
J22: RB_I2C5; PinSocket_1x04_P2.54mm_Vertical
J23: RB_I2C6; PinSocket_1x04_P2.54mm_Vertical
J24: RB_I2C7; PinSocket_1x04_P2.54mm_Vertical
J25: RB_Power; PinSocket_1x04_P2.54mm_Vertical
J26: JST_RB_I2C5; JST_PH_B4B-PH-K_1x04_P2.00mm_Vertical
J27: JST_RB_I2C6; JST_PH_B4B-PH-K_1x04_P2.00mm_Vertical
J28: JST_RB_I2C7; JST_PH_B4B-PH-K_1x04_P2.00mm_Vertical
M1: NXT_M2; RJ25_Wayconn_MJEA-660X1_Horizontal
M2: NXT_M1; RJ25_Wayconn_MJEA-660X1_Horizontal
M3: NXT_M0; RJ25_Wayconn_MJEA-660X1_Horizontal
ON/OFF: SW_SPDT; XKB Connection SS-12M11G5
R1, R3, R7, R8, R11, R12: 10k; R_0805_2012Metric_Pad1.20x1.40mm_HandSolder
R2, R4, R9, R10, R13, R14: 1M; R_0805_2012Metric_Pad1.20x1.40mm_HandSolder
RB 7V: RB_M3; PinSocket_1x02_P2.54mm_Vertical
SW1_A9, SW2_A10, SW3_A11: SW_Push; SW_PUSH_6mm
U1 74HC14: 74HC14; SO-14_3.9x8.65mm_P1.27mm
VIN_7V: XT60_Case; AMASS_XT60IPW-M_1x03_P7.20mm_Horizontal

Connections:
+3.3V: C9 100n.1, D1.1 (K), D3.1 (K), D6.1 (K), D7.1 (K), D10.1 (K), D11.1 (K), J25.2, U1 74HC14.7 (GND)
+5V: J8.3, J25.3, M1.4, M2.4, M3.4
/AKKU1: J3.2, ON/OFF.2 (B)
/AKKU2: ON/OFF.3 (C), VIN_7V.2
/M0A: M3.1, RB 7V.1
/M0B: M3.2, RB 7V.2
/M1A: J4.1, M2.1
/M1B: J4.2, M2.2
/M2A: J6.1, M1.1
/M2B: J6.2, M1.2
Button1: A1.A9, SW1_A9.1
Button2: A1.A10, SW2_A10.1
Button3: A1.A11, SW3_A11.1
ENC_M0_A: M3.5, R1.1
ENC_M0_B: M3.6, R3.1
ENC_M0_DIR: A1.D16 (D16/TX2), U1 74HC14.4
ENC_M0_INT: A1.D19 (D19/RX1), U1 74HC14.2
ENC_M1_A: M2.5, R7.1
ENC_M1_B: M2.6, R8.1
ENC_M1_DIR: A1.D15 (D15/RX3), U1 74HC14.8
ENC_M1_INT: A1.D18 (D18/TX1), U1 74HC14.6
ENC_M2_A: M1.5, R11.1
ENC_M2_B: M1.6, R12.1
ENC_M2_DIR: A1.D14 (D14/TX3), U1 74HC14.12
ENC_M2_INT: A1.D17 (D17/RX2), U1 74HC14.10
GND: C1.2, C2.2, C3.2, C4.2, C5.2, C6.2, C9 100n.2, D2.2 (A), D4.2 (A), D8.2 (A), D9.2 (A), D12.2 (A), D13.2 (A), J3.1, J8.4, J9.2, J13.2, J14.2, J15.2, J16.2, J17.2, J18.2, J19.2, J20.2, J21.2, J22.2, J23.2, J24.2, J25.1, J26.2, J27.2, J28.2, M1.3, M2.3, M3.3, R2.2, R4.2, R9.2, R10.2, R13.2, R14.2, SW1_A9.2, SW2_A10.2, SW3_A11.2, U1 74HC14.14 (VCC), VIN_7V.1
unnamed: C1.1, D1.2 (A), D2.1 (K), R1.2, R2.1, U1 74HC14.1
unnamed: C2.1, D3.2 (A), D4.1 (K), R3.2, R4.1, U1 74HC14.3
unnamed: C3.1, D6.2 (A), D8.1 (K), R7.2, R9.1, U1 74HC14.5
unnamed: C4.1, D7.2 (A), D9.1 (K), R8.2, R10.1, U1 74HC14.9
unnamed: C5.1, D10.2 (A), D12.1 (K), R11.2, R13.1, U1 74HC14.11
unnamed: C6.1, D11.2 (A), D13.1 (K), R12.2, R14.1, U1 74HC14.13
SCL0: J9.3, J18.3
SCL1: J13.3, J17.3
SCL2: J14.3, J19.3
SCL3: J15.3, J20.3
SCL4: J16.3, J21.3
SCL5: J22.3, J26.3
SCL6: J23.3, J27.3
SCL7: J8.2, J24.3, J28.3
SDA0: J9.1, J18.1
SDA1: J13.1, J17.1
SDA2: J14.1, J19.1
SDA3: J15.1, J20.1
SDA4: J16.1, J21.1
SDA5: J22.1, J26.1
SDA6: J23.1, J27.1
SDA7: J8.1, J24.1, J28.1
VDDI2C0: J9.4, J18.4
VDDI2C1: J13.4, J17.4
VDDI2C2: J14.4, J19.4
VDDI2C3: J15.4, J20.4
VDDI2C4: J16.4, J21.4
VDDI2C5: J22.4, J26.4
VDDI2C6: J23.4, J27.4
VDDI2C7: J24.4, J28.4
